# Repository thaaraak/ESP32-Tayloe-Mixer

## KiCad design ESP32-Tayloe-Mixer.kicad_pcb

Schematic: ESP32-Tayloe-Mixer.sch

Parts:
C1, C2, C4, C12, C13, C17, C19, C30, C78, C203, C204: .1uF; Capacitor 0805
C5, C7: 82pF; Capacitor 1206
C11: 100uF; Cap_6.3x5.4
C14, C16, C18, C79: 22uF; Cap_4x5.4
C22, C23, C24, C25: .022uF; Capacitor 1206
H1, H2, H3, H4: MountingHole; MountingHole_2.7mm_M2.5_Pad
J1: Jack-DC; BarrelJack_Horizontal
J2: BNC
J3: Audio_Jack
J4: Conn_01x03; PinHeader_1x03_P2.54mm_Vertical
L1: Inductor; T37_Inductor
R1, R2, R3, R4, R5, R6, R11, R12, R13, R14, R15, R16: 10k; Resistor 0805
R7, R17, R18, R19, R20, R147, R148: 49.9; Resistor 0805
R201, R202: 100; Resistor 0805
RV1: R_POT; Trimpot Vertical
T1: T50_SPLITTER; T50 Trifilar
U1, U2: LM358; SO08
U3: AMS1117; SOT-223-3_TabPin2
U6: MCP1703A-2502_SOT223; TO-252-3_TabPin2
U8: FST3253; SO16
U201: ESP32-15-PIN; ESP32-15Pin; PARTREV 4
U202: PCBARTISTS-ES8388; PCBArtist-ES8388
U203: si5351
VR1: Trimpot; Trimpot Vertical

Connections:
0: C22.2, R17.2, U8.3 (1B4), U8.10 (2B1)
90: C24.1, R19.2, U8.4 (1B3), U8.11 (2B2)
180: C23.1, R18.2, U8.6 (1B1), U8.13 (2B4)
270: C25.2, R20.2, U8.5 (1B2), U8.12 (2B3)
+2V5: C18.1, C19.1, R15.2, R16.1, U1.3 (+IN), U1.5 (+IN), U2.3 (+IN), U2.5 (+IN)
+3.3VA: C78.1, C79.1, U3.2 (VO), U202.17 (AVDD)
+3V3: U201.1 (3V3), U202.2 (DVDD), VR1.1 (CW)
+5V: C14.1, C30.2, R5.1, R15.1, U3.3 (VI), U6.3 (VO), U8.16 (VCC), U201.19 (EXT_5V), U203.VIN
+12V: C11.1, C12.1, C13.1, C16.1, C17.1, J1.1, U1.8 (P$V+), U2.8 (P$V+), U6.1 (VI)
DIN: U201.29 (IO5), U202.6 (DSDIN)
DOUT: U201.31 (IO16), U202.8 (ASDOUT)
GND: C4.2, C5.2, C11.2, C12.2, C13.2, C14.2, C16.2, C17.2, C18.2, C19.2, C22.1, C23.2, C24.2, C25.1, C30.1, C78.2, C79.2, C203.2, C204.2, J1.2, J2.GND, J3.SLEEVE, J4.1, R6.2, R7.2, R16.2, RV1.3, T1.C1B, U1.4 (P$V-), U2.4 (P$V-), U3.1 (ADJ), U6.2 (GND), U8.1 (OE1), U8.8 (GND), U8.15 (OE2), U201.14 (GND1), U202.4 (GND), U203.GND, VR1.3 (CCW)
I_Out: C2.2, C204.1, R202.2
LO_0: U8.14 (S0), U203.2
LO_90: U8.2 (S1), U203.0
LRCLK: U201.30 (IO17), U202.7 (LRCLK)
MCLK: U201.24 (RXD0), U202.1 (MCLK)
unnamed: C1.1, R1.1
unnamed: C2.1, R2.1
unnamed: C4.1, R5.2, R6.1, T1.C2A, T1.C3B
unnamed: C5.1, L1.1, T1.C1A
unnamed: C7.1, R7.1, RV1.1
unnamed: C7.2, L1.2
unnamed: J2.S (OUT), RV1.2
unnamed: J3.RING, J3.RSH, U202.22 (LIN2)
unnamed: J3.TIP, J3.TSH, U202.21 (RIN2)
unnamed: R1.2, R3.1, U1.2 (-IN)
unnamed: R2.2, R4.1, U2.2 (-IN)
unnamed: R3.2, R11.1, R17.1, U1.1 (OUT)
unnamed: R11.2, R13.1, U1.6 (-IN)
unnamed: R4.2, R12.1, R19.1, U2.1 (OUT)
unnamed: R12.2, R14.1, U2.6 (-IN)
unnamed: R13.2, R18.1, U1.7 (OUT)
unnamed: R14.2, R20.1, U2.7 (OUT)
unnamed: R147.1, T1.C3A
unnamed: R147.2, U8.9 (2A)
unnamed: R148.1, T1.C2B
unnamed: R148.2, U8.7 (1A)
unnamed: R201.1, U202.15 (LOUT2)
unnamed: R202.1, U202.14 (ROUT2)
unnamed: U201.5 (IO34), VR1.2 (WIPER)
Q_Out: C1.2, C203.1, R201.2
SCL: U201.22 (IO22), U202.28 (SCL)
SCL2: J4.3, U201.10 (IO26), U203.SCL
SCLK: U201.28 (IO18), U202.5 (SCLK)
SDA: U201.21 (IO23), U202.27 (SDA)
SDA2: J4.2, U201.11 (IO27), U203.SDA

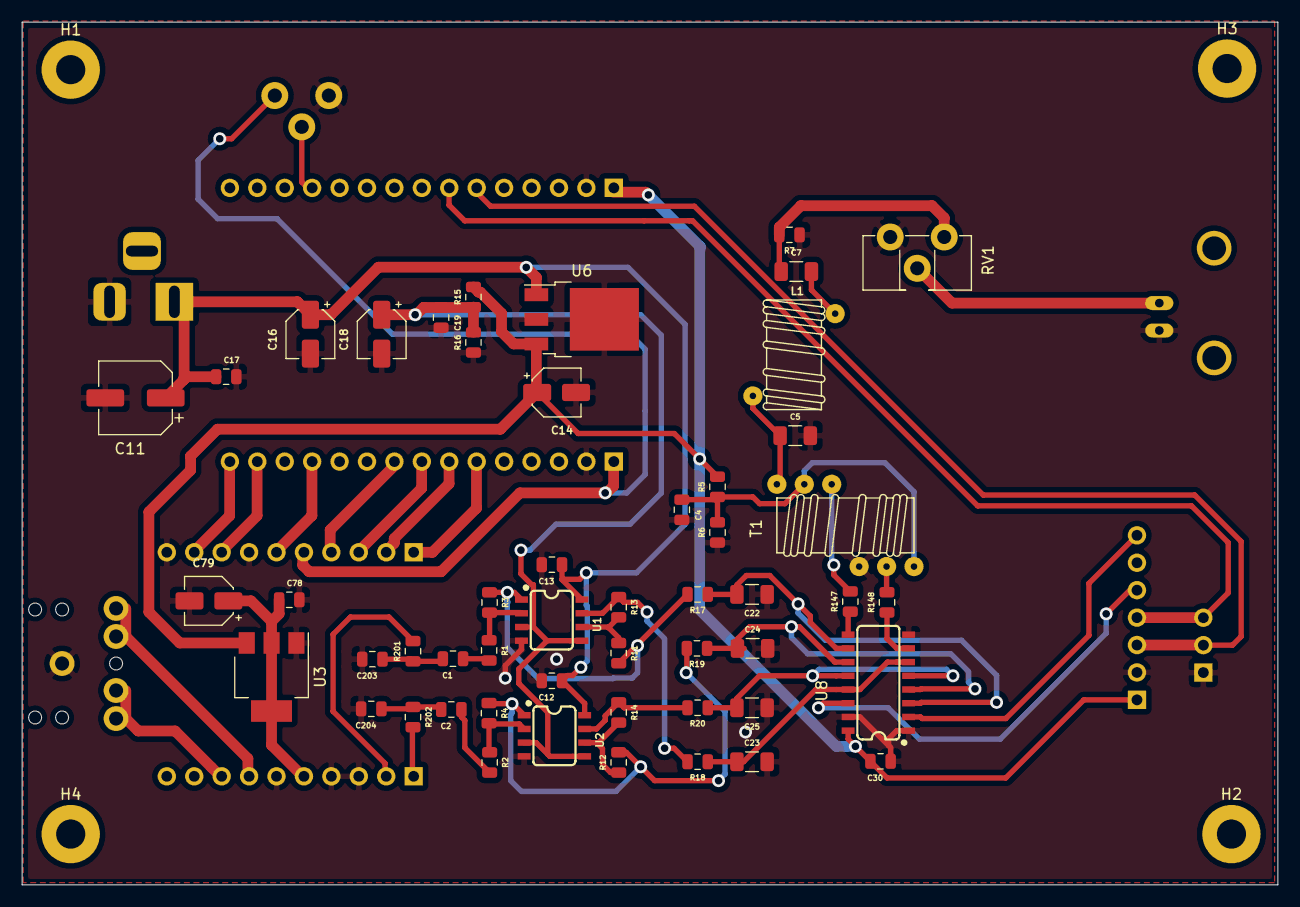
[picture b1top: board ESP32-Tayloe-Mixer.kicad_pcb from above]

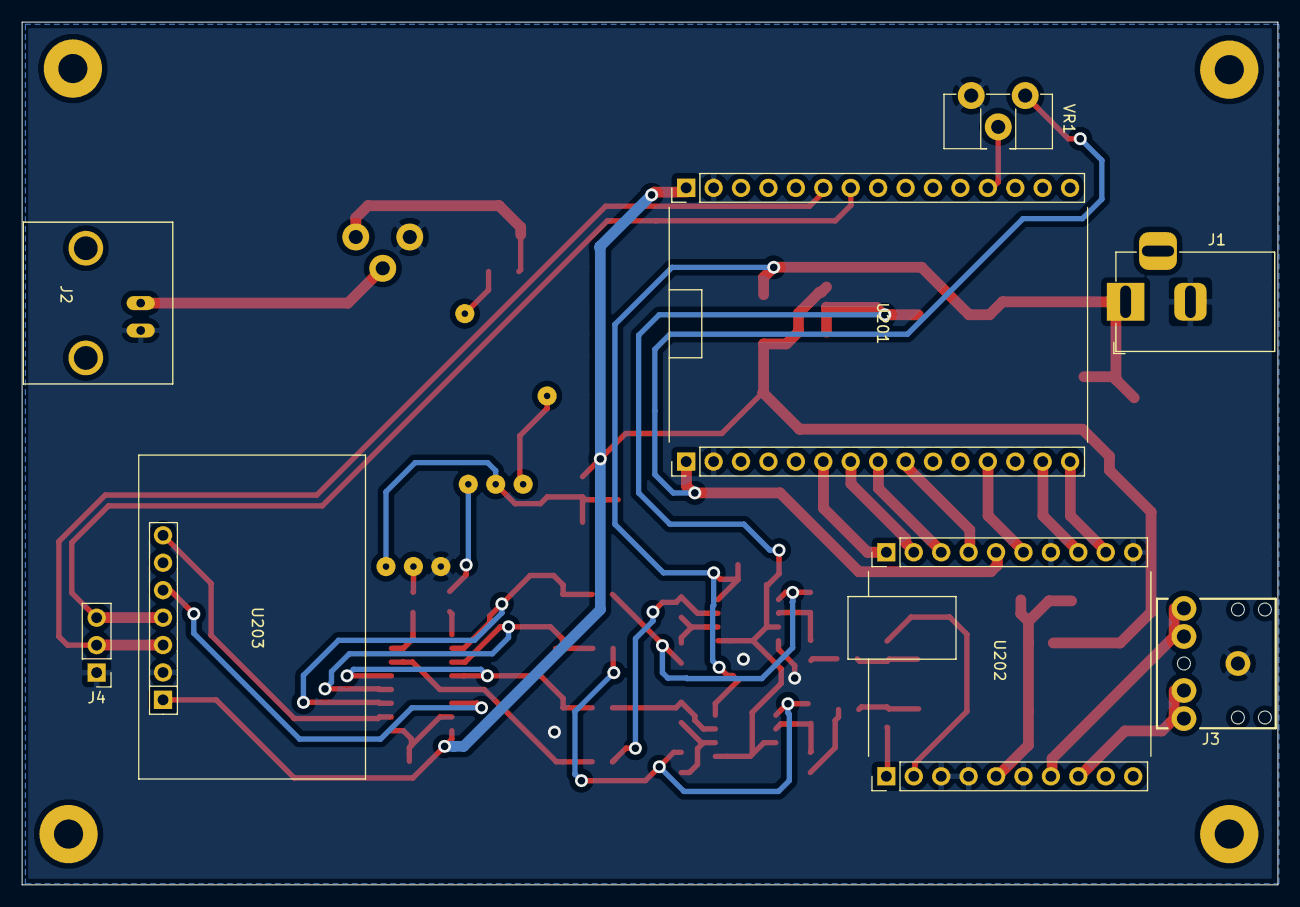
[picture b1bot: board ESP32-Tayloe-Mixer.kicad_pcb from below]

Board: 2 copper layers, 116.3 x 79.9 mm, 63 parts (8 on the bottom side), 47 nets.

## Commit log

2021-09-05 added pdf
2021-09-05 fixed schematic
